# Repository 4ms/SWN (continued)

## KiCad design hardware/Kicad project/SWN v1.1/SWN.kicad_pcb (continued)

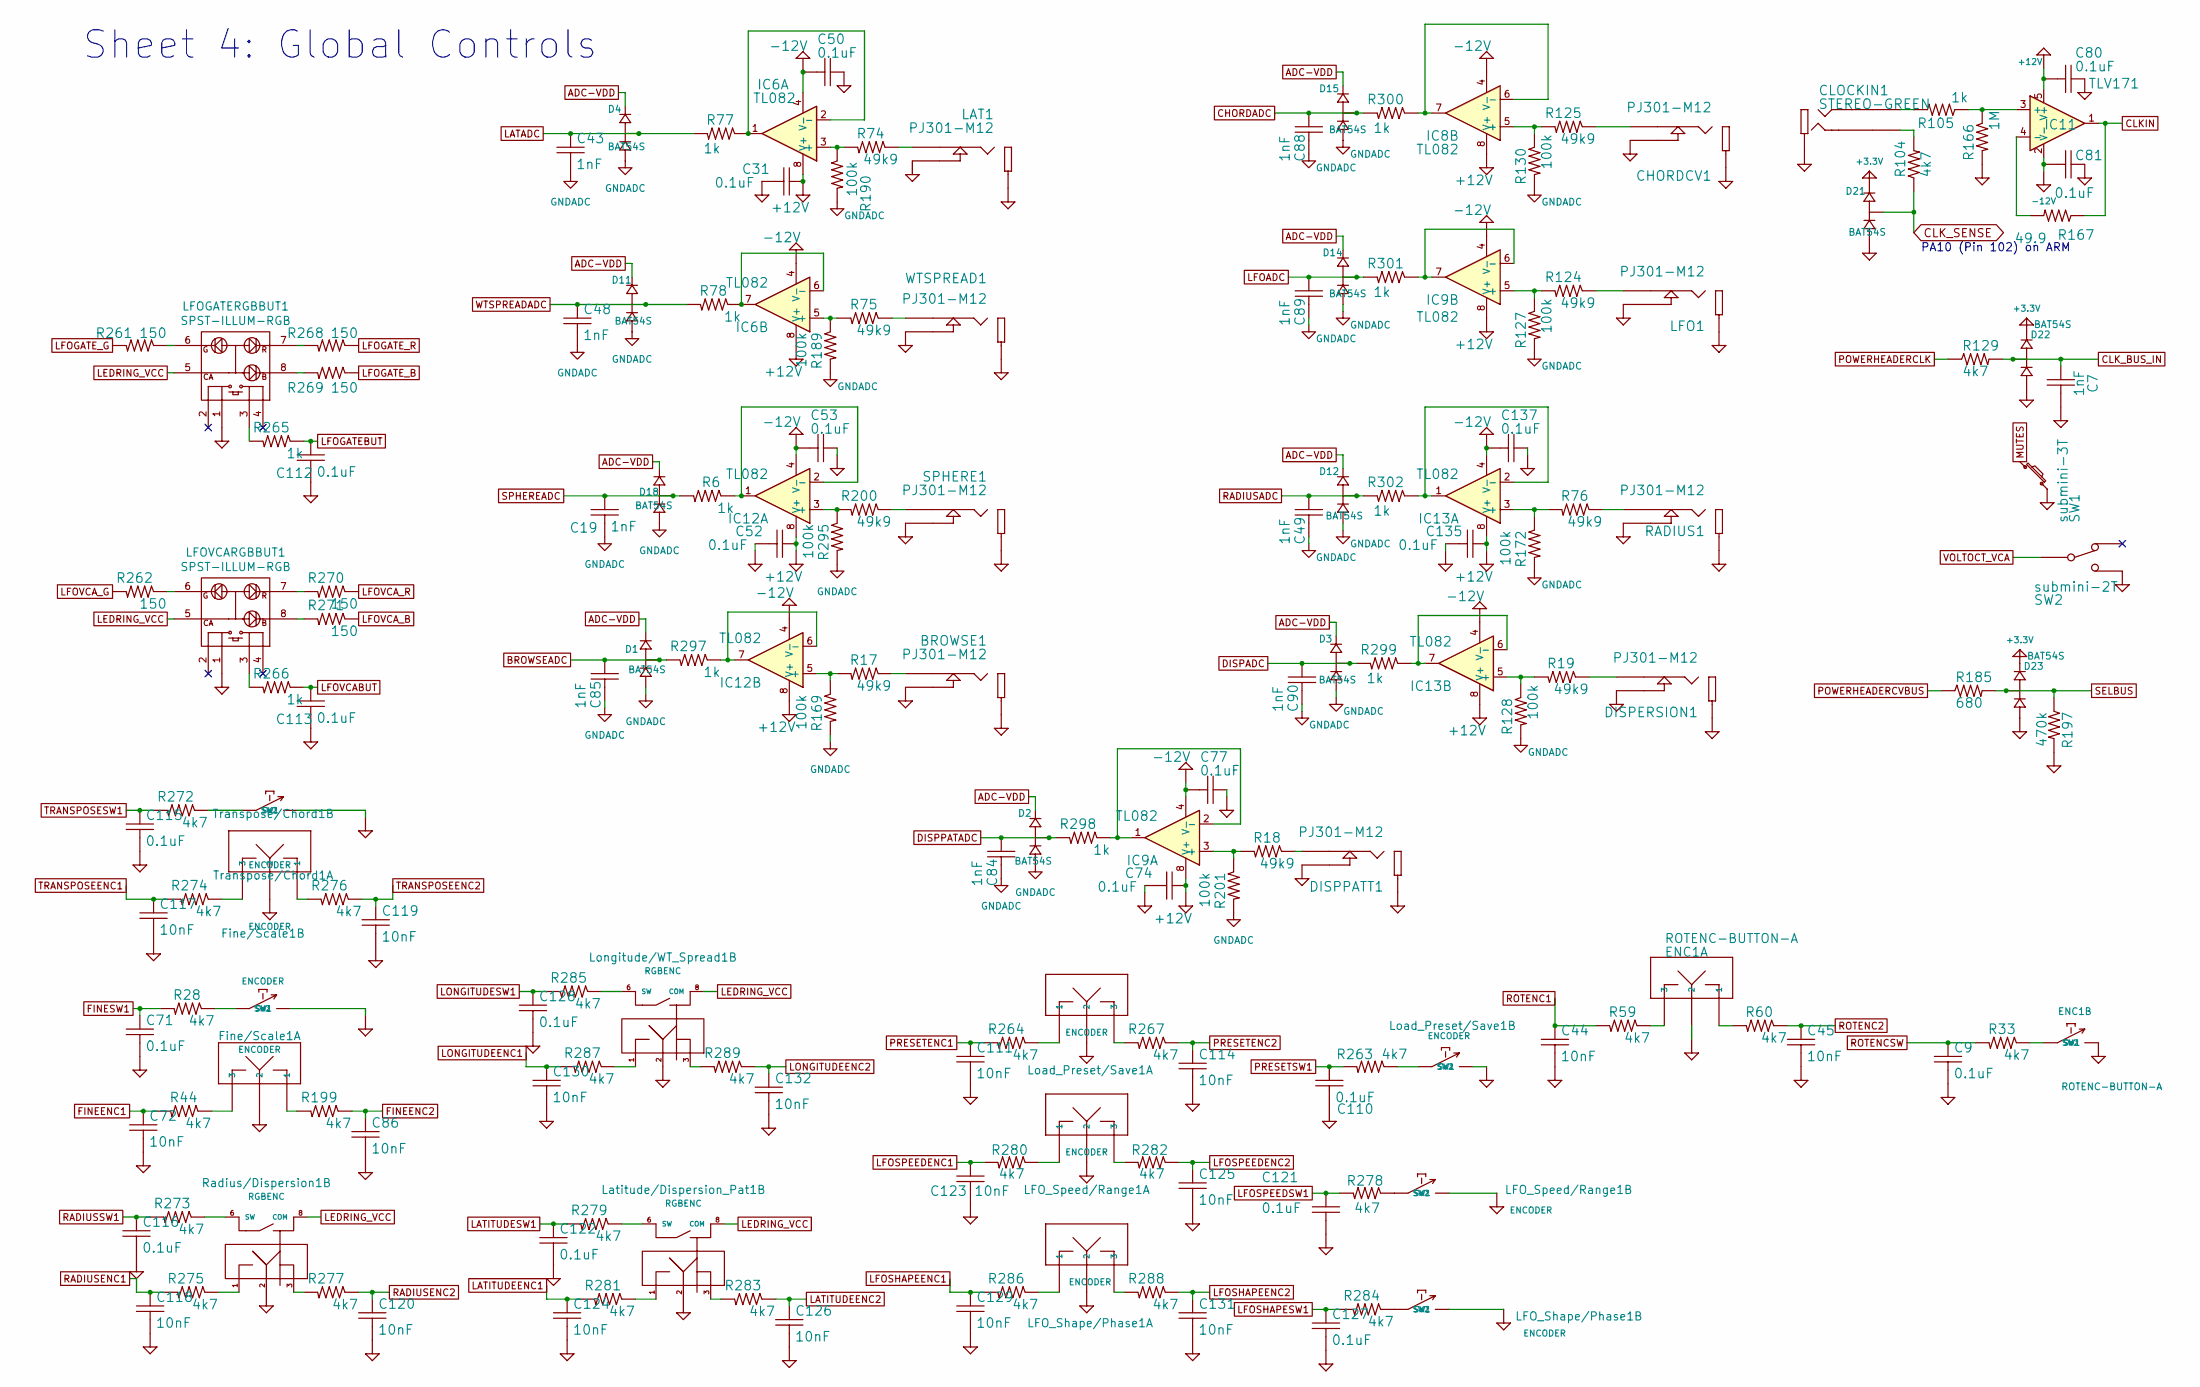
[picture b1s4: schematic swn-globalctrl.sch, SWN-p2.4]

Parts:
BROWSE1: PJ301-M12; PJ301M-12
C7, C19, C43, C48, C49, C84, C85, C88, C89, C90: 1nF; C0603
C9, C31, C50, C52, C53, C71, C74, C77, C80, C81, C110, C112, C113, C115, C116, C121, C122, C127, C128, C135, C137: 0.1uF; C0603
C44, C45, C72, C86, C111, C114, C117, C118, C119, C120, C123, C124, C125, C126, C129, C130, C131, C132: 10nF; C0603
CHORDCV1: PJ301-M12; PJ301M-12
CLOCKIN1: STEREO-GREEN; PJ301M-12
D1, D2, D3, D4, D11, D12, D14, D15, D18, D21, D22, D23: BAT54S; SOT23
DISPERSION1: PJ301-M12; PJ301M-12
DISPPATT1: PJ301-M12; PJ301M-12
ENC1: ROTENC-BUTTON-A; ENC_SPST_12mm_NUDGED
Fine/Scale1: ENCODER; ENC_RGB_SPST_12mm_NUDGED
IC6, IC8, IC9, IC12, IC13: TL082; TSSOP-8_4.4x3mm_Pitch0.65mm
IC11: TLV171; SOT-23-5
LAT1: PJ301-M12; PJ301M-12
LFO1: PJ301-M12; PJ301M-12
LFOGATERGBBUT1: SPST-ILLUM-RGB; RGB-SPST-LED-TC002
LFOVCARGBBUT1: SPST-ILLUM-RGB; RGB-SPST-LED-TC002
LFO_Shape/Phase1: ENCODER; ENC_SPST_12mm_NUDGED
LFO_Speed/Range1: ENCODER; ENC_SPST_12mm_NUDGED
Latitude/Dispersion_Pat1: RGBENC; ENC_RGB_SPST_12mm_NUDGED
Load_Preset/Save1: ENCODER; ENC_SPST_12mm_NUDGED
Longitude/WT_Spread1: RGBENC; ENC_RGB_SPST_12mm_NUDGED
R6, R77, R78, R105, R265, R266, R297, R298, R299, R300, R301, R302: 1k; R0603
R17, R18, R19, R74, R75, R76, R124, R125, R200: 49k9; R0603
R28, R33, R44, R59, R60, R104, R129, R199, R263, R264, R267, R272, R273, R274, R275, R276, R277, R278, R279, R280, R281, R282, R283, R284, R285, R286, R287, R288, R289: 4k7; R0603
R127, R128, R130, R169, R172, R189, R190, R201, R295: 100k; R0603
R166: 1M; R0603
R167: 49.9; R0603
R185: 680; R0603
R197: 470k; R0603
R261, R262, R268, R269, R270, R271: 150; R0603
RADIUS1: PJ301-M12; PJ301M-12
Radius/Dispersion1: RGBENC; ENC_RGB_SPST_12mm_NUDGED
SPHERE1: PJ301-M12; PJ301M-12
SW1: submini-3T; Switch_Toggle_SPST_SubMini
SW2: submini-2T; SPDT-SUB
Transpose/Chord1: ENCODER; ENC_SPST_12mm_NUDGED
WTSPREAD1: PJ301-M12; PJ301M-12

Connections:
+3.3V: D21.2 (CATHODE), D22.2 (CATHODE), D23.2 (CATHODE); also elsewhere on the board
+12V: C31.1, C52.1, C74.1, C80.2, C135.1, IC6.8 (V+), IC8.8 (V+), IC9.8 (V+), IC11.5 (V+), IC12.8 (V+), IC13.8 (V+); also elsewhere on the board
-12V: C50.2, C53.2, C77.2, C81.2, C137.2, IC6.4 (V-), IC8.4 (V-), IC9.4 (V-), IC11.2 (V-), IC12.4 (V-), IC13.4 (V-); also elsewhere on the board
ADC-VDD: D1.2 (CATHODE), D2.2 (CATHODE), D3.2 (CATHODE), D4.2 (CATHODE), D11.2 (CATHODE), D12.2 (CATHODE), D14.2 (CATHODE), D15.2 (CATHODE), D18.2 (CATHODE); also elsewhere on the board
BROWSEADC: C85.1, D1.3 (COMMON), R297.2; also elsewhere on the board
CHORDADC: C88.1, D15.3 (COMMON), R300.2; also elsewhere on the board
CLKIN: IC11.1, R167.1; also elsewhere on the board
CLK_BUS_IN: C7.1, D22.3 (COMMON), R129.2; also elsewhere on the board
CLK_SENSE: D21.3 (COMMON), R104.1; also elsewhere on the board
DISPADC: C90.1, D3.3 (COMMON), R299.2; also elsewhere on the board
DISPPATADC: C84.1, D2.3 (COMMON), R298.2; also elsewhere on the board
FINEENC1: C72.1, R44.2; also elsewhere on the board
FINEENC2: C86.1, R199.1; also elsewhere on the board
FINESW1: C71.1, R28.2; also elsewhere on the board
GNDADC: C19.2, C43.2, C48.2, C49.2, C84.2, C85.2, C88.2, C89.2, C90.2, D1.1 (ANODE), D2.1 (ANODE), D3.1 (ANODE), D4.1 (ANODE), D11.1 (ANODE), D12.1 (ANODE), D14.1 (ANODE), D15.1 (ANODE), D18.1 (ANODE), R127.2, R128.2, R130.2, R169.2, R172.2, R189.2, R190.2, R201.2, R295.2; also elsewhere on the board
LATADC: C43.1, D4.3 (COMMON), R77.2; also elsewhere on the board
LATITUDEENC1: C124.1, R281.2; also elsewhere on the board
LATITUDEENC2: C126.1, R283.1; also elsewhere on the board
LATITUDESW1: C122.1, R279.2; also elsewhere on the board
LEDRING_VCC: LFOGATERGBBUT1.5 (CA), LFOVCARGBBUT1.5 (CA), Latitude/Dispersion_Pat1.8, Longitude/WT_Spread1.8, Radius/Dispersion1.8; also elsewhere on the board
LFOADC: C89.1, D14.3 (COMMON), R301.2; also elsewhere on the board
LFOGATEBUT: C112.1, R265.1; also elsewhere on the board
LFOGATE_B: R269.1; also elsewhere on the board
LFOGATE_G: R261.2; also elsewhere on the board
LFOGATE_R: R268.1; also elsewhere on the board
LFOSHAPEENC1: C129.1, R286.2; also elsewhere on the board
LFOSHAPEENC2: C131.1, R288.1; also elsewhere on the board
LFOSHAPESW1: C127.1, R284.2; also elsewhere on the board
LFOSPEEDENC1: C123.1, R280.2; also elsewhere on the board
LFOSPEEDENC2: C125.1, R282.1; also elsewhere on the board
LFOSPEEDSW1: C121.1, R278.2; also elsewhere on the board
LFOVCABUT: C113.1, R266.1; also elsewhere on the board
LFOVCA_B: R271.1; also elsewhere on the board
LFOVCA_G: R262.2; also elsewhere on the board
LFOVCA_R: R270.1; also elsewhere on the board
LONGITUDEENC1: C130.1, R287.2; also elsewhere on the board
LONGITUDEENC2: C132.1, R289.1; also elsewhere on the board
LONGITUDESW1: C128.1, R285.2; also elsewhere on the board
MUTES: SW1.2; also elsewhere on the board
unnamed: BROWSE1.1 (TIP), R17.1
unnamed: CHORDCV1.1 (TIP), R125.1
unnamed: CLOCKIN1.1 (TIP), R105.2
unnamed: CLOCKIN1.3 (TIP-SW), R104.2
unnamed: DISPERSION1.1 (TIP), R19.1
unnamed: DISPPATT1.1 (TIP), R18.1
unnamed: ENC1.1, R60.2
unnamed: ENC1.3, R59.1
unnamed: ENC1.SW1, R33.1
unnamed: Fine/Scale1.1, R199.2
unnamed: Fine/Scale1.3, R44.1
unnamed: Fine/Scale1.SW1, R28.1
unnamed: IC6.1, IC6.2 (-), R77.1
unnamed: IC6.3 (+), R74.2, R190.1
unnamed: IC6.5 (+), R75.2, R189.1
unnamed: IC6.6 (-), IC6.7, R78.1
unnamed: IC8.5 (+), R125.2, R130.1
unnamed: IC8.6 (-), IC8.7, R300.1
unnamed: IC9.1, IC9.2 (-), R298.1
unnamed: IC9.3 (+), R18.2, R201.1
unnamed: IC9.5 (+), R124.2, R127.1
unnamed: IC9.6 (-), IC9.7, R301.1
unnamed: IC11.3 (+), R105.1, R166.1
unnamed: IC11.4 (-), R167.2
unnamed: IC12.1, IC12.2 (-), R6.1
unnamed: IC12.3 (+), R200.2, R295.1
unnamed: IC12.5 (+), R17.2, R169.1
unnamed: IC12.6 (-), IC12.7, R297.1
unnamed: IC13.1, IC13.2 (-), R302.1
unnamed: IC13.3 (+), R76.2, R172.1
unnamed: IC13.5 (+), R19.2, R128.1
unnamed: IC13.6 (-), IC13.7, R299.1
unnamed: LAT1.1 (TIP), R74.1
unnamed: LFO1.1 (TIP), R124.1
unnamed: LFOGATERGBBUT1.3 (DOWN-A), R265.2
unnamed: LFOGATERGBBUT1.6 (G), R261.1
unnamed: LFOGATERGBBUT1.7 (R), R268.2
unnamed: LFOGATERGBBUT1.8 (B), R269.2
unnamed: LFOVCARGBBUT1.3 (DOWN-A), R266.2
unnamed: LFOVCARGBBUT1.6 (G), R262.1
unnamed: LFOVCARGBBUT1.7 (R), R270.2
unnamed: LFOVCARGBBUT1.8 (B), R271.2
unnamed: LFO_Shape/Phase1.1, R286.1
unnamed: LFO_Shape/Phase1.3, R288.2
unnamed: LFO_Shape/Phase1.SW1, R284.1
unnamed: LFO_Speed/Range1.1, R280.1
unnamed: LFO_Speed/Range1.3, R282.2
unnamed: LFO_Speed/Range1.SW1, R278.1
unnamed: Latitude/Dispersion_Pat1.1, R281.1
unnamed: Latitude/Dispersion_Pat1.3, R283.2
unnamed: Latitude/Dispersion_Pat1.6 (SW), R279.1
unnamed: Load_Preset/Save1.1, R264.1
unnamed: Load_Preset/Save1.3, R267.2
unnamed: Load_Preset/Save1.SW1, R263.1
unnamed: Longitude/WT_Spread1.1, R287.1
unnamed: Longitude/WT_Spread1.3, R289.2
unnamed: Longitude/WT_Spread1.6 (SW), R285.1
unnamed: R75.1, WTSPREAD1.1 (TIP)
unnamed: R76.1, RADIUS1.1 (TIP)
unnamed: R200.1, SPHERE1.1 (TIP)
unnamed: R272.1, Transpose/Chord1.SW1
unnamed: R273.1, Radius/Dispersion1.6 (SW)
unnamed: R274.1, Transpose/Chord1.3
unnamed: R275.1, Radius/Dispersion1.1
unnamed: R276.2, Transpose/Chord1.1
unnamed: R277.2, Radius/Dispersion1.3
POWERHEADERCLK: R129.1; also elsewhere on the board
POWERHEADERCVBUS: R185.1; also elsewhere on the board
PRESETENC1: C111.1, R264.2; also elsewhere on the board
PRESETENC2: C114.1, R267.1; also elsewhere on the board
PRESETSW1: C110.1, R263.2; also elsewhere on the board
RADIUSADC: C49.1, D12.3 (COMMON), R302.2; also elsewhere on the board
RADIUSENC1: C118.1, R275.2; also elsewhere on the board
RADIUSENC2: C120.1, R277.1; also elsewhere on the board
RADIUSSW1: C116.1, R273.2; also elsewhere on the board
ROTENC1: C44.1, R59.2; also elsewhere on the board
ROTENC2: C45.1, R60.1; also elsewhere on the board
ROTENCSW: C9.1, R33.2; also elsewhere on the board
SELBUS: D23.3 (COMMON), R185.2, R197.1; also elsewhere on the board
SPHEREADC: C19.1, D18.3 (COMMON), R6.2; also elsewhere on the board
TRANSPOSEENC1: C117.1, R274.2; also elsewhere on the board
TRANSPOSEENC2: C119.1, R276.1; also elsewhere on the board
TRANSPOSESW1: C115.1, R272.2; also elsewhere on the board
VOLTOCT_VCA: SW2.2; also elsewhere on the board
WTSPREADADC: C48.1, D11.3 (COMMON), R78.2; also elsewhere on the board

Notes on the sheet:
Sheet 4: Global Controls
PA10 (Pin 102) on ARM

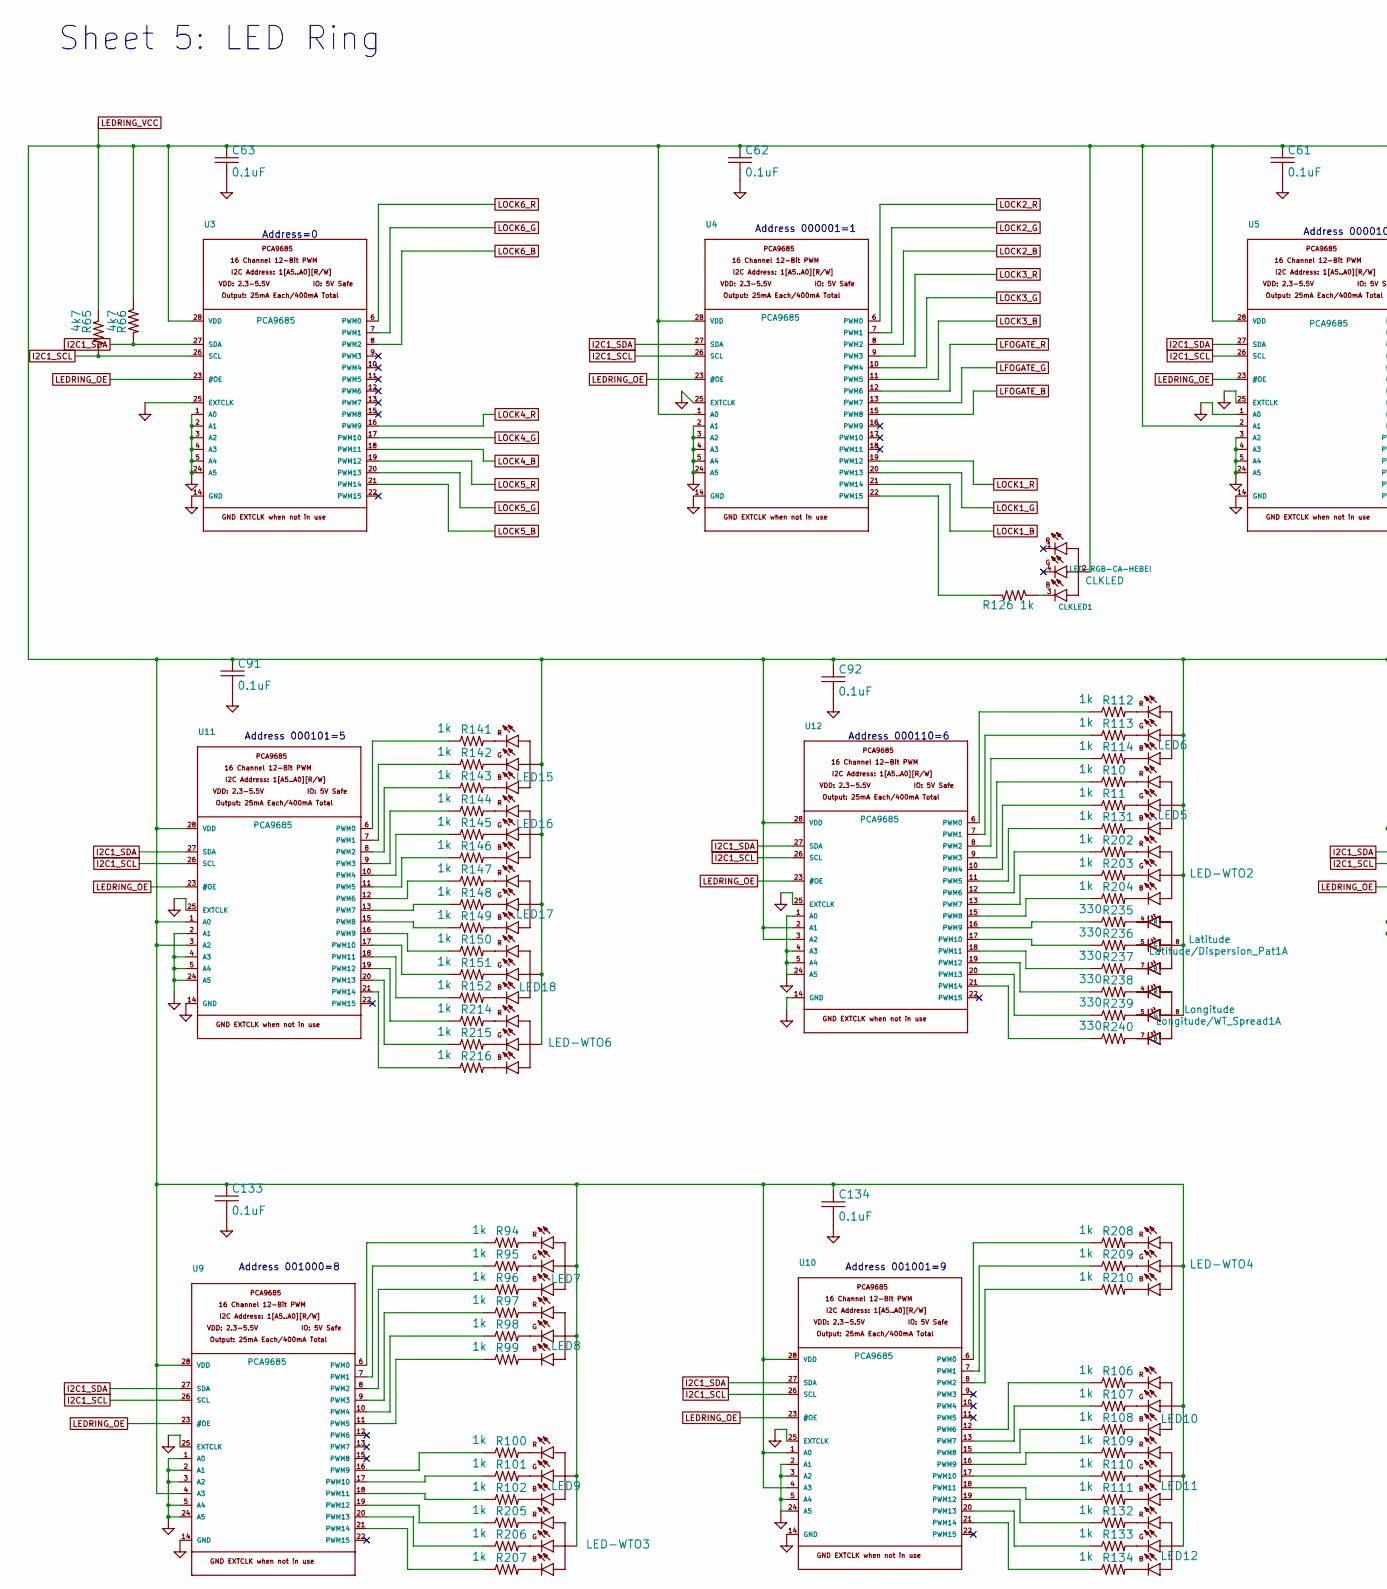
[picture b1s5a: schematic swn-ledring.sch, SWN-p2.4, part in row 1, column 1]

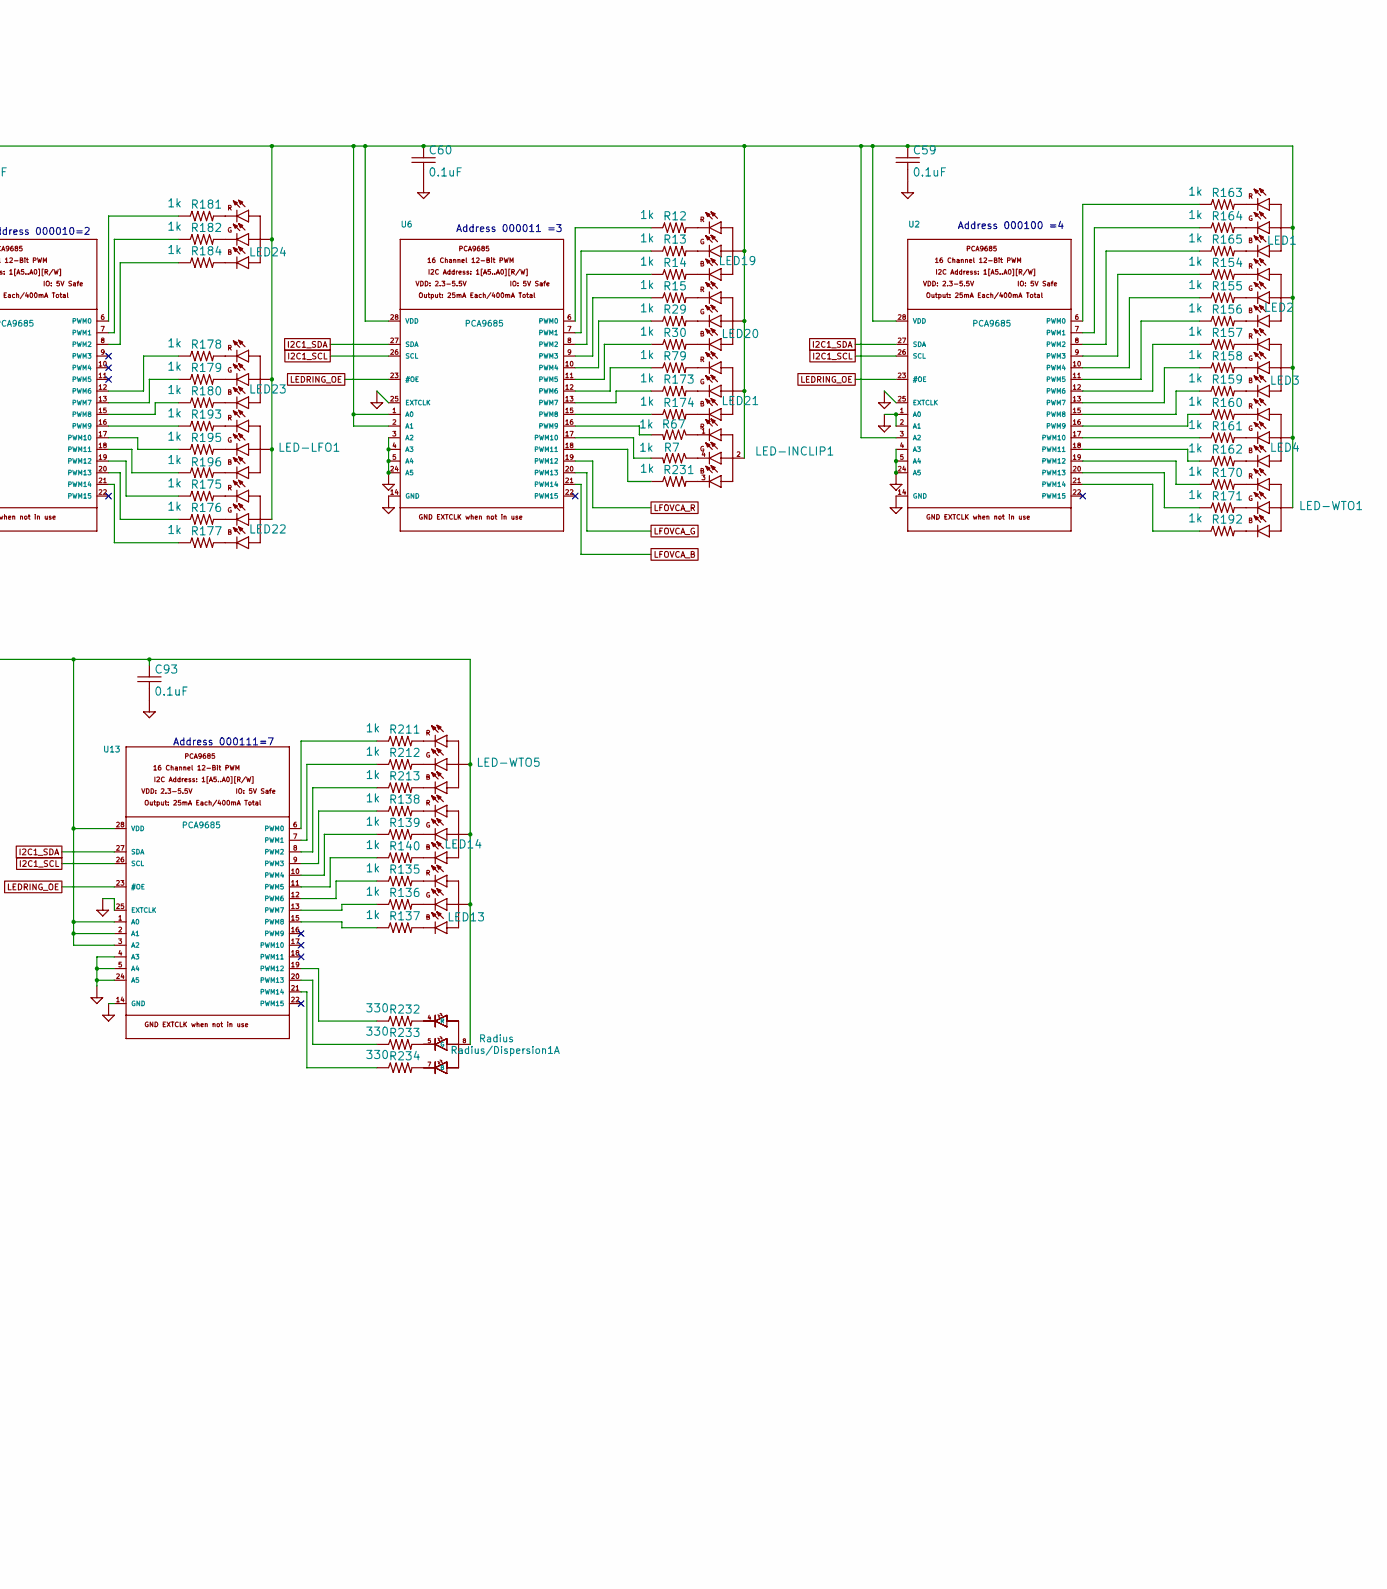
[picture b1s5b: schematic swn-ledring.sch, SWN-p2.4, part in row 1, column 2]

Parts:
C59, C60, C61, C62, C63, C91, C92, C93, C133, C134: 0.1uF; C0603
CLKLED1: LED-RGB-CA-HEBEI; LED_PLCC-4
LED1, LED2, LED3, LED4, LED5, LED6, LED7, LED8, LED9, LED10, LED11, LED12, LED13, LED14, LED15, LED16, LED17, LED18, LED19, LED20, LED21, LED22, LED23, LED24: LED-RGB-CA-HEBEI; LED_PLCC-4
LED-INCLIP1: LED-RGB-CA-HEBEI; LED_PLCC-4
LED-LFO1: LED-RGB-CA-HEBEI; LED_PLCC-4
LED-WTO1, LED-WTO2, LED-WTO3, LED-WTO4, LED-WTO5, LED-WTO6: LED-RGB-CA-HEBEI; LED_PLCC-4
Latitude/Dispersion_Pat1: RGBENC; ENC_RGB_SPST_12mm_NUDGED
Longitude/WT_Spread1: RGBENC; ENC_RGB_SPST_12mm_NUDGED
R7, R10, R11, R12, R13, R14, R15, R29, R30, R67, R79, R94, R95, R96, R97, R98, R99, R100, R101, R102, R106, R107, R108, R109, R110, R111, R112, R113, R114, R126, R131, R132, R133, R134, R135, R136, R137, R138, R139, R140, R141, R142, R143, R144, R145, R146, R147, R148, R149, R150, R151, R152, R154, R155, R156, R157, R158, R159, R160, R161, R162, R163, R164, R165, R170, R171, R173, R174, R175, R176, R177, R178, R179, R180, R181, R182, R184, R192, R193, R195, R196, R202, R203, R204, R205, R206, R207, R208, R209, R210, R211, R212, R213, R214, R215, R216, R231: 1k; R0603
R65, R66: 4k7; R0603
R232, R233, R234, R235, R236, R237, R238, R239, R240: 330; R0603
Radius/Dispersion1: RGBENC; ENC_RGB_SPST_12mm_NUDGED
U2, U3, U4, U5, U6, U9, U10, U11, U12, U13: PCA9685; TSSOP-28_4.4x9.7mm_Pitch0.65mm

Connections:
I2C1_SCL: R65.2, U2.26 (SCL), U3.26 (SCL), U4.26 (SCL), U5.26 (SCL), U6.26 (SCL), U9.26 (SCL), U10.26 (SCL), U11.26 (SCL), U12.26 (SCL), U13.26 (SCL); also elsewhere on the board
I2C1_SDA: R66.2, U2.27 (SDA), U3.27 (SDA), U4.27 (SDA), U5.27 (SDA), U6.27 (SDA), U9.27 (SDA), U10.27 (SDA), U11.27 (SDA), U12.27 (SDA), U13.27 (SDA); also elsewhere on the board
LEDRING_OE: U2.23 (#OE), U3.23 (#OE), U4.23 (#OE), U5.23 (#OE), U6.23 (#OE), U9.23 (#OE), U10.23 (#OE), U11.23 (#OE), U12.23 (#OE), U13.23 (#OE); also elsewhere on the board
LEDRING_VCC: C59.1, C60.1, C61.1, C62.1, C63.1, C91.1, C92.1, C93.1, C133.1, C134.1, CLKLED1.2 (A), LED1.2 (A), LED2.2 (A), LED3.2 (A), LED4.2 (A), LED5.2 (A), LED6.2 (A), LED7.2 (A), LED8.2 (A), LED9.2 (A), LED10.2 (A), LED11.2 (A), LED12.2 (A), LED13.2 (A), LED14.2 (A), LED15.2 (A), LED16.2 (A), LED17.2 (A), LED18.2 (A), LED19.2 (A), LED20.2 (A), LED21.2 (A), LED22.2 (A), LED23.2 (A), LED24.2 (A), LED-INCLIP1.2 (A), LED-LFO1.2 (A), LED-WTO1.2 (A), LED-WTO2.2 (A), LED-WTO3.2 (A), LED-WTO4.2 (A), LED-WTO5.2 (A), LED-WTO6.2 (A), Latitude/Dispersion_Pat1.8, Longitude/WT_Spread1.8, R65.1, R66.1, Radius/Dispersion1.8, U2.3 (A2), U2.28 (VDD), U3.28 (VDD), U4.1 (A0), U4.28 (VDD), U5.2 (A1), U5.28 (VDD), U6.1 (A0), U6.2 (A1), U6.28 (VDD), U9.4 (A3), U9.28 (VDD), U10.1 (A0), U10.4 (A3), U10.28 (VDD), U11.1 (A0), U11.3 (A2), U11.28 (VDD), U12.2 (A1), U12.3 (A2), U12.28 (VDD), U13.1 (A0), U13.2 (A1), U13.3 (A2), U13.28 (VDD); also elsewhere on the board
LFOGATE_B: U4.15 (PWM8); also elsewhere on the board
LFOGATE_G: U4.13 (PWM7); also elsewhere on the board
LFOGATE_R: U4.12 (PWM6); also elsewhere on the board
LFOVCA_B: U6.21 (PWM14); also elsewhere on the board
LFOVCA_G: U6.20 (PWM13); also elsewhere on the board
LFOVCA_R: U6.19 (PWM12); also elsewhere on the board
LOCK1_B: U4.21 (PWM14); also elsewhere on the board
LOCK1_G: U4.20 (PWM13); also elsewhere on the board
LOCK1_R: U4.19 (PWM12); also elsewhere on the board
LOCK2_B: U4.8 (PWM2); also elsewhere on the board
LOCK2_G: U4.7 (PWM1); also elsewhere on the board
LOCK2_R: U4.6 (PWM0); also elsewhere on the board
LOCK3_B: U4.11 (PWM5); also elsewhere on the board
LOCK3_G: U4.10 (PWM4); also elsewhere on the board
LOCK3_R: U4.9 (PWM3); also elsewhere on the board
LOCK4_B: U3.18 (PWM11); also elsewhere on the board
LOCK4_G: U3.17 (PWM10); also elsewhere on the board
LOCK4_R: U3.16 (PWM9); also elsewhere on the board
LOCK5_B: U3.21 (PWM14); also elsewhere on the board
LOCK5_G: U3.20 (PWM13); also elsewhere on the board
LOCK5_R: U3.19 (PWM12); also elsewhere on the board
LOCK6_B: U3.8 (PWM2); also elsewhere on the board
LOCK6_G: U3.7 (PWM1); also elsewhere on the board
LOCK6_R: U3.6 (PWM0); also elsewhere on the board
unnamed: CLKLED1.3 (CB), R126.1
unnamed: LED1.1 (CR), R163.2
unnamed: LED1.3 (CB), R165.2
unnamed: LED1.4 (CG), R164.2
unnamed: LED2.1 (CR), R154.2
unnamed: LED2.3 (CB), R156.2
unnamed: LED2.4 (CG), R155.2
unnamed: LED3.1 (CR), R157.2
unnamed: LED3.3 (CB), R159.2
unnamed: LED3.4 (CG), R158.2
unnamed: LED4.1 (CR), R160.2
unnamed: LED4.3 (CB), R162.2
unnamed: LED4.4 (CG), R161.2
unnamed: LED5.1 (CR), R10.2
unnamed: LED5.3 (CB), R131.2
unnamed: LED5.4 (CG), R11.2
unnamed: LED6.1 (CR), R112.2
unnamed: LED6.3 (CB), R114.2
unnamed: LED6.4 (CG), R113.2
unnamed: LED7.1 (CR), R94.2
unnamed: LED7.3 (CB), R96.2
unnamed: LED7.4 (CG), R95.2
unnamed: LED8.1 (CR), R97.2
unnamed: LED8.3 (CB), R99.2
unnamed: LED8.4 (CG), R98.2
unnamed: LED9.1 (CR), R100.2
unnamed: LED9.3 (CB), R102.2
unnamed: LED9.4 (CG), R101.2
unnamed: LED10.1 (CR), R106.2
unnamed: LED10.3 (CB), R108.2
unnamed: LED10.4 (CG), R107.2
unnamed: LED11.1 (CR), R109.2
unnamed: LED11.3 (CB), R111.2
unnamed: LED11.4 (CG), R110.2
unnamed: LED12.1 (CR), R132.2
unnamed: LED12.3 (CB), R134.2
unnamed: LED12.4 (CG), R133.2
unnamed: LED13.1 (CR), R135.2
unnamed: LED13.3 (CB), R137.2
unnamed: LED13.4 (CG), R136.2
unnamed: LED14.1 (CR), R138.2
unnamed: LED14.3 (CB), R140.2
unnamed: LED14.4 (CG), R139.2
unnamed: LED15.1 (CR), R141.2
unnamed: LED15.3 (CB), R143.2
unnamed: LED15.4 (CG), R142.2
unnamed: LED16.1 (CR), R144.2
unnamed: LED16.3 (CB), R146.2
unnamed: LED16.4 (CG), R145.2
unnamed: LED17.1 (CR), R147.2
unnamed: LED17.3 (CB), R149.2
unnamed: LED17.4 (CG), R148.2
unnamed: LED18.1 (CR), R150.2
unnamed: LED18.3 (CB), R152.2
unnamed: LED18.4 (CG), R151.2
unnamed: LED19.1 (CR), R12.2
unnamed: LED19.3 (CB), R14.2
unnamed: LED19.4 (CG), R13.2
unnamed: LED20.1 (CR), R15.2
unnamed: LED20.3 (CB), R30.2
unnamed: LED20.4 (CG), R29.2
unnamed: LED21.1 (CR), R79.2
unnamed: LED21.3 (CB), R174.2
unnamed: LED21.4 (CG), R173.2
unnamed: LED22.1 (CR), R175.2
unnamed: LED22.3 (CB), R177.2
unnamed: LED22.4 (CG), R176.2
unnamed: LED23.1 (CR), R178.2
unnamed: LED23.3 (CB), R180.2
unnamed: LED23.4 (CG), R179.2
unnamed: LED24.1 (CR), R181.2
unnamed: LED24.3 (CB), R184.2
unnamed: LED24.4 (CG), R182.2
unnamed: LED-INCLIP1.1 (CR), R67.1
unnamed: LED-INCLIP1.3 (CB), R231.2
unnamed: LED-INCLIP1.4 (CG), R7.1
unnamed: LED-LFO1.1 (CR), R193.2
unnamed: LED-LFO1.3 (CB), R196.2
unnamed: LED-LFO1.4 (CG), R195.2
unnamed: LED-WTO1.1 (CR), R170.2
unnamed: LED-WTO1.3 (CB), R192.2
unnamed: LED-WTO1.4 (CG), R171.2
unnamed: LED-WTO2.1 (CR), R202.2
unnamed: LED-WTO2.3 (CB), R204.2
unnamed: LED-WTO2.4 (CG), R203.2
unnamed: LED-WTO3.1 (CR), R205.2
unnamed: LED-WTO3.3 (CB), R207.2
unnamed: LED-WTO3.4 (CG), R206.2
unnamed: LED-WTO4.1 (CR), R208.2
unnamed: LED-WTO4.3 (CB), R210.2
unnamed: LED-WTO4.4 (CG), R209.2
unnamed: LED-WTO5.1 (CR), R211.2
unnamed: LED-WTO5.3 (CB), R213.2
unnamed: LED-WTO5.4 (CG), R212.2
unnamed: LED-WTO6.1 (CR), R214.2
unnamed: LED-WTO6.3 (CB), R216.2
unnamed: LED-WTO6.4 (CG), R215.2
unnamed: Latitude/Dispersion_Pat1.4 (R), R235.2
unnamed: Latitude/Dispersion_Pat1.5 (G), R236.2
unnamed: Latitude/Dispersion_Pat1.7 (B), R237.2
unnamed: Longitude/WT_Spread1.4 (R), R238.2
unnamed: Longitude/WT_Spread1.5 (G), R239.2
unnamed: Longitude/WT_Spread1.7 (B), R240.2
unnamed: R7.2, U6.17 (PWM10)
unnamed: R10.1, U12.9 (PWM3)
unnamed: R11.1, U12.10 (PWM4)
unnamed: R12.1, U6.6 (PWM0)
unnamed: R13.1, U6.7 (PWM1)
unnamed: R14.1, U6.8 (PWM2)
unnamed: R15.1, U6.9 (PWM3)
unnamed: R29.1, U6.10 (PWM4)
unnamed: R30.1, U6.11 (PWM5)
unnamed: R67.2, U6.16 (PWM9)
unnamed: R79.1, U6.12 (PWM6)
unnamed: R94.1, U9.6 (PWM0)
unnamed: R95.1, U9.7 (PWM1)
unnamed: R96.1, U9.8 (PWM2)
unnamed: R97.1, U9.9 (PWM3)
unnamed: R98.1, U9.10 (PWM4)
unnamed: R99.1, U9.11 (PWM5)
unnamed: R100.1, U9.16 (PWM9)
unnamed: R101.1, U9.17 (PWM10)
unnamed: R102.1, U9.18 (PWM11)
unnamed: R106.1, U10.12 (PWM6)
unnamed: R107.1, U10.13 (PWM7)
unnamed: R108.1, U10.15 (PWM8)
unnamed: R109.1, U10.16 (PWM9)
unnamed: R110.1, U10.17 (PWM10)
unnamed: R111.1, U10.18 (PWM11)
unnamed: R112.1, U12.6 (PWM0)
unnamed: R113.1, U12.7 (PWM1)
unnamed: R114.1, U12.8 (PWM2)
unnamed: R126.2, U4.22 (PWM15)
unnamed: R131.1, U12.11 (PWM5)
unnamed: R132.1, U10.19 (PWM12)
unnamed: R133.1, U10.20 (PWM13)
unnamed: R134.1, U10.21 (PWM14)
unnamed: R135.1, U13.12 (PWM6)
unnamed: R136.1, U13.13 (PWM7)
unnamed: R137.1, U13.15 (PWM8)
unnamed: R138.1, U13.9 (PWM3)
unnamed: R139.1, U13.10 (PWM4)
unnamed: R140.1, U13.11 (PWM5)
unnamed: R141.1, U11.6 (PWM0)
unnamed: R142.1, U11.7 (PWM1)
unnamed: R143.1, U11.8 (PWM2)
unnamed: R144.1, U11.9 (PWM3)
unnamed: R145.1, U11.10 (PWM4)
unnamed: R146.1, U11.11 (PWM5)
unnamed: R147.1, U11.12 (PWM6)
unnamed: R148.1, U11.13 (PWM7)
unnamed: R149.1, U11.15 (PWM8)
unnamed: R150.1, U11.16 (PWM9)
unnamed: R151.1, U11.17 (PWM10)
unnamed: R152.1, U11.18 (PWM11)
unnamed: R154.1, U2.9 (PWM3)
unnamed: R155.1, U2.10 (PWM4)
unnamed: R156.1, U2.11 (PWM5)
unnamed: R157.1, U2.12 (PWM6)
unnamed: R158.1, U2.13 (PWM7)
unnamed: R159.1, U2.15 (PWM8)
unnamed: R160.1, U2.16 (PWM9)
unnamed: R161.1, U2.17 (PWM10)
unnamed: R162.1, U2.18 (PWM11)
unnamed: R163.1, U2.6 (PWM0)
unnamed: R164.1, U2.7 (PWM1)
unnamed: R165.1, U2.8 (PWM2)
unnamed: R170.1, U2.19 (PWM12)
unnamed: R171.1, U2.20 (PWM13)
unnamed: R173.1, U6.13 (PWM7)
unnamed: R174.1, U6.15 (PWM8)
unnamed: R175.1, U5.19 (PWM12)
unnamed: R176.1, U5.20 (PWM13)
unnamed: R177.1, U5.21 (PWM14)
unnamed: R178.1, U5.12 (PWM6)
unnamed: R179.1, U5.13 (PWM7)
unnamed: R180.1, U5.15 (PWM8)
unnamed: R181.1, U5.6 (PWM0)
unnamed: R182.1, U5.7 (PWM1)
unnamed: R184.1, U5.8 (PWM2)
unnamed: R192.1, U2.21 (PWM14)
unnamed: R193.1, U5.16 (PWM9)
unnamed: R195.1, U5.17 (PWM10)
unnamed: R196.1, U5.18 (PWM11)
unnamed: R202.1, U12.12 (PWM6)
unnamed: R203.1, U12.13 (PWM7)
unnamed: R204.1, U12.15 (PWM8)
unnamed: R205.1, U9.19 (PWM12)
unnamed: R206.1, U9.20 (PWM13)
unnamed: R207.1, U9.21 (PWM14)
unnamed: R208.1, U10.6 (PWM0)
unnamed: R209.1, U10.7 (PWM1)
unnamed: R210.1, U10.8 (PWM2)
unnamed: R211.1, U13.6 (PWM0)
unnamed: R212.1, U13.7 (PWM1)
unnamed: R213.1, U13.8 (PWM2)
unnamed: R214.1, U11.19 (PWM12)
unnamed: R215.1, U11.20 (PWM13)
unnamed: R216.1, U11.21 (PWM14)
unnamed: R231.1, U6.18 (PWM11)
unnamed: R232.1, U13.19 (PWM12)
unnamed: R232.2, Radius/Dispersion1.4 (R)
unnamed: R233.1, U13.20 (PWM13)
unnamed: R233.2, Radius/Dispersion1.5 (G)
unnamed: R234.1, U13.21 (PWM14)
unnamed: R234.2, Radius/Dispersion1.7 (B)
unnamed: R235.1, U12.16 (PWM9)
unnamed: R236.1, U12.17 (PWM10)
unnamed: R237.1, U12.18 (PWM11)
unnamed: R238.1, U12.19 (PWM12)
unnamed: R239.1, U12.20 (PWM13)
unnamed: R240.1, U12.21 (PWM14)

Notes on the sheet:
Sheet 5: LED Ring
Address 000100 =4
Address 000011 =3
Address 000001=1
Address=0
Address 000010=2
Address 000101=5
Address 000110=6
Address 000111=7
Address 001000=8
Address 001001=9

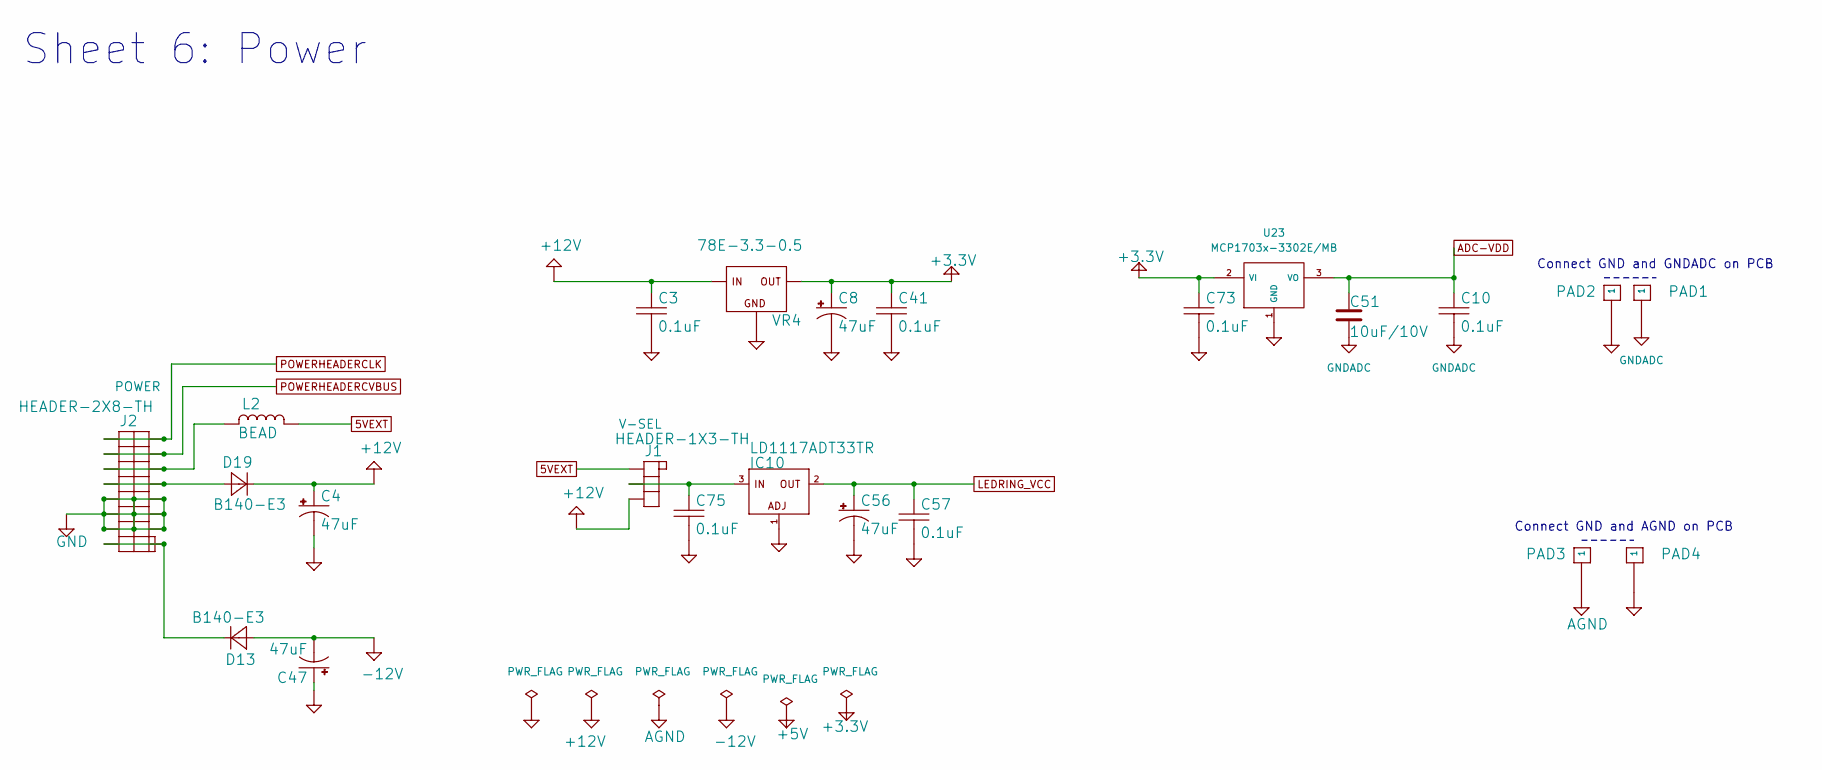
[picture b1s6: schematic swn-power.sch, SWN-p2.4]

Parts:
C3, C10, C41, C57, C73, C75: 0.1uF; C0603
C4, C8, C47, C56: 47uF; CP_Elec_5x5.3
C51: 10uF/10V; C0603
D13, D19: B140-E3; SMA_Standard
IC10: LD1117ADT33TR; TO-252-2
J1: HEADER-1X3-TH; Pins_1x03_2.54mm_TH
J2: HEADER-2X8-TH; HEADER-2X8-TH_eagle_pinout
L2: BEAD; R0603
PAD1, PAD2, PAD3, PAD4: PAD-06
U23: MCP1703x-3302E/MB; SOT-89-3
VR4: 78E-3.3-0.5; RECOM-DCDC

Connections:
5VEXT: J1.1, L2.2 (4)
+3.3V: C8.1 (+), C41.1, C73.1, U23.2 (VI), VR4.3 (OUT); also elsewhere on the board
+12V: C3.1, C4.1 (+), D19.1 (C), J1.3, VR4.1 (IN); also elsewhere on the board
-12V: C47.2 (-), D13.2 (A); also elsewhere on the board
ADC-VDD: C10.1, C51.1, U23.3 (VO); also elsewhere on the board
AGND: PAD3.1; also elsewhere on the board
GNDADC: C10.2, C51.2, PAD1.1; also elsewhere on the board
LEDRING_VCC: C56.1 (+), C57.1, IC10.2 (OUT); also elsewhere on the board
unnamed: C75.1, IC10.3 (IN), J1.2
unnamed: D13.1 (C), J2.1, J2.2
unnamed: D19.2 (A), J2.9, J2.10
unnamed: J2.11, J2.12, L2.1
POWERHEADERCLK: J2.15, J2.16; also elsewhere on the board
POWERHEADERCVBUS: J2.13, J2.14; also elsewhere on the board

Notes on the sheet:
Sheet 6: Power
Connect GND and GNDADC on PCB
Connect GND and AGND on PCB
